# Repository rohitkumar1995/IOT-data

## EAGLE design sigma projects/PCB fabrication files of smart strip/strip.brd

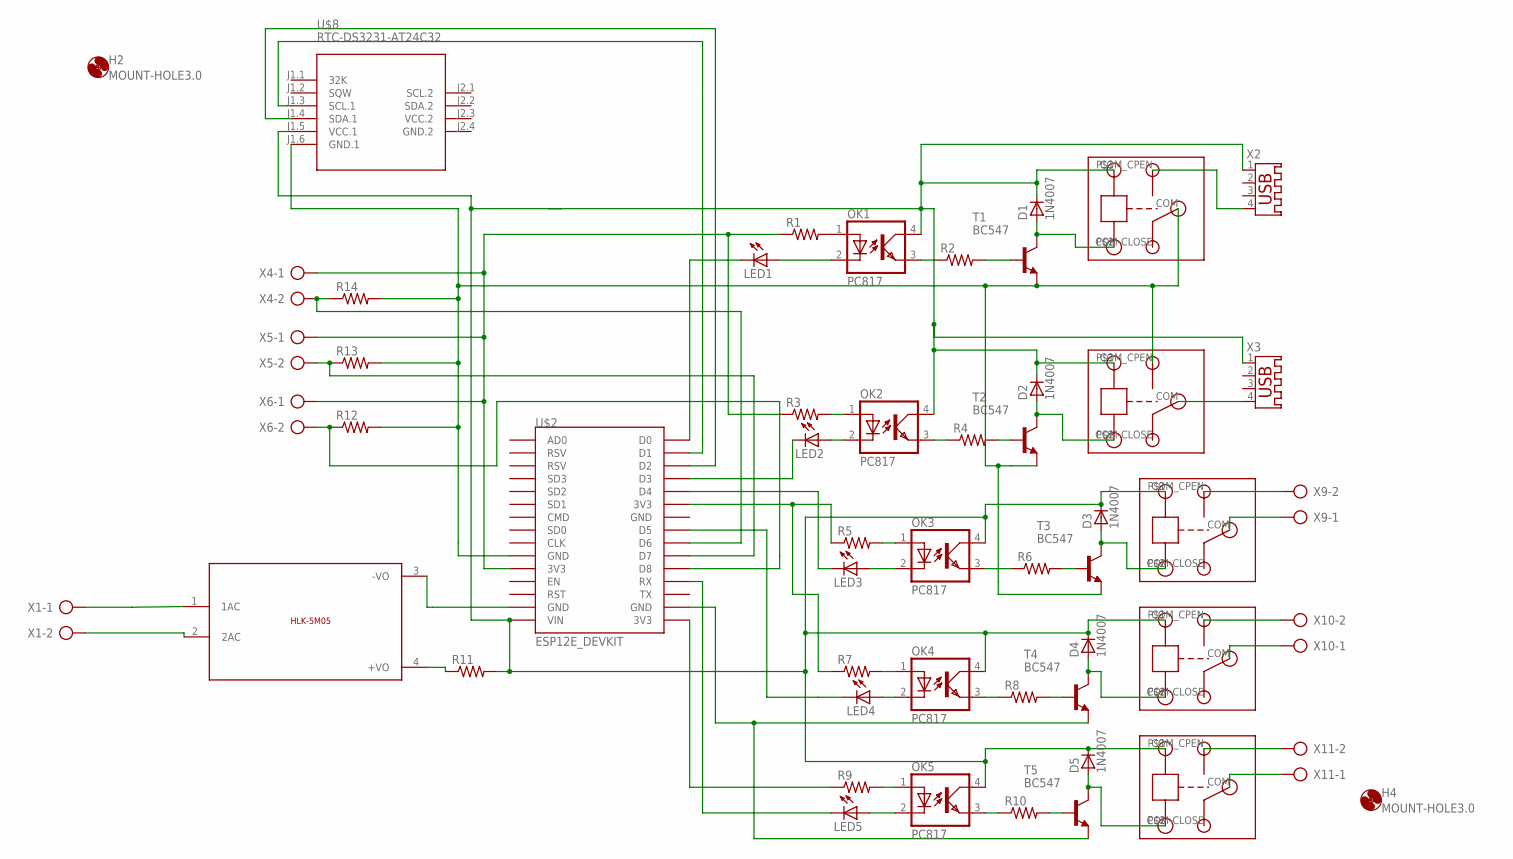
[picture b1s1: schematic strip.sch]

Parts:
D1, D2, D3, D4, D5: 1N4007; SMA
H2, H4: MOUNT-HOLE3.0; 3,0
LED1, LED2, LED3, LED4, LED5: LED3MM
OK1, OK2, OK3, OK4, OK5: PC817; DIL04
R1, R2, R3, R4, R5, R6, R7, R8, R9, R10, R11, R12, R13, R14: R-US_0204/5; 0204/5
T1, T2, T3, T4, T5: BC547; TO92
U$1: 5VDC/5W; HLK-5M05
U$2: ESP12E_DEVKIT
U$3, U$4, U$5, U$6, U$7: RELAY
U$8: RTC-DS3231-AT24C32
X1, X4, X5, X6, X9, X10, X11: AK300/2
X2, X3: USB-A003

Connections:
GND.2: U$8.J2.4 (GND.2)
unnamed: U$1.1 (1AC), X1.1
unnamed: U$1.2 (2AC), X1.2
unnamed: R11.1, U$1.4 (+VO)
unnamed: U$1.3 (-VO), U$2.GND@1 (GND)
unnamed: LED1.A, OK1.2 (C)
unnamed: LED1.K (C), U$2.D0
unnamed: OK1.1 (A), R1.2
unnamed: R1.1, R3.1, U$2.3V3@0 (3V3), X4.1, X5.1, X6.1
unnamed: D1.K (C), D2.K (C), D3.K (C), D4.K (C), D5.K (C), OK1.4 (COL), OK2.4 (COL), OK3.4 (COL), OK4.4 (COL), OK5.4 (COL), R11.2, U$2.VIN, U$3.P$1 (IN), U$4.P$1 (IN), U$5.P$1 (IN), U$6.P$1 (IN), U$7.P$1 (IN), U$8.J1.5 (VCC.1), X2.1, X3.1
unnamed: OK1.3 (EMIT), R2.1
unnamed: R2.2, T1.2 (B)
unnamed: R12.2, R13.2, R14.2, T1.1 (E), T2.1 (E), T3.1 (E), U$2.GND@0 (GND), U$3.COM, U$4.COM_CPEN (COM-OPEN), U$8.J1.6 (GND.1)
unnamed: D1.A, T1.3 (C), U$3.P$2 (GND)
unnamed: U$7.COM_CPEN (COM-OPEN), X11.2
unnamed: U$7.COM, X11.1
unnamed: U$6.COM_CPEN (COM-OPEN), X10.2
unnamed: U$6.COM, X10.1
unnamed: U$5.COM_CPEN (COM-OPEN), X9.2
unnamed: U$5.COM, X9.1
unnamed: U$4.COM, X3.4
unnamed: R12.1, U$2.D8, X6.2
unnamed: U$3.COM_CPEN (COM-OPEN), X2.4
unnamed: R13.1, U$2.D7, X5.2
unnamed: LED2.A, OK2.2 (C)
unnamed: LED2.K (C), U$2.D3
unnamed: OK2.1 (A), R3.2
unnamed: OK2.3 (EMIT), R4.1
unnamed: R4.2, T2.2 (B)
unnamed: D2.A, T2.3 (C), U$4.P$2 (GND)
unnamed: LED3.A, OK3.2 (C)
unnamed: LED3.K (C), U$2.D4
unnamed: OK3.1 (A), R5.2
unnamed: OK5.1 (A), R9.2
unnamed: OK3.3 (EMIT), R6.1
unnamed: R6.2, T3.2 (B)
unnamed: D3.A, T3.3 (C), U$5.P$2 (GND)
unnamed: LED4.A, OK4.2 (C)
unnamed: OK4.1 (A), R7.2
unnamed: R5.1, R7.1, U$2.3V3@1 (3V3)
unnamed: OK4.3 (EMIT), R8.1
unnamed: R8.2, T4.2 (B)
unnamed: D4.A, T4.3 (C), U$6.P$2 (GND)
unnamed: T4.1 (E), T5.1 (E), U$2.GND@3 (GND)
unnamed: OK5.3 (EMIT), R10.1
unnamed: R10.2, T5.2 (B)
unnamed: D5.A, T5.3 (C), U$7.P$2 (GND)
unnamed: LED5.A, OK5.2 (C)
unnamed: LED4.K (C), U$2.D5
unnamed: U$2.D1, U$8.J1.3 (SCL.1)
unnamed: LED5.K (C), U$2.RX
unnamed: R9.1, U$2.3V3@2 (3V3)
unnamed: U$2.D2, U$8.J1.4 (SDA.1)
unnamed: R14.1, U$2.D6, X4.2
VCC.2: U$8.J2.3 (VCC.2)

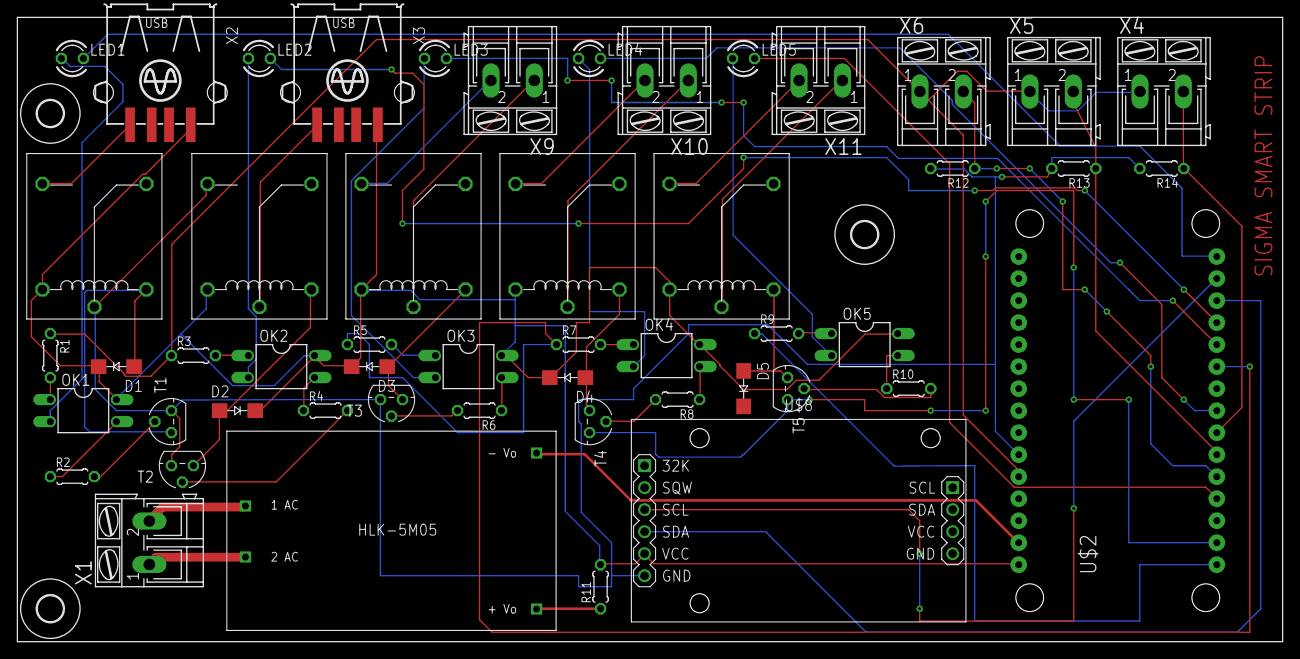
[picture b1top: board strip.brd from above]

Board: 2 copper layers, 146.0 x 72.1 mm, 54 parts (0 on the bottom side), 53 nets.

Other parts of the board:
H3: MOUNT-HOLE3.0; 3,0

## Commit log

2018-10-12 added files

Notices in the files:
parts and their libraries:
diy-modules: Released under the Creative Commons Attribution 4.0 International License: http://creativecommons.org/licenses/by/4.0
